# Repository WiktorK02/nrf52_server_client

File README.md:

to do:
remove delay from functions

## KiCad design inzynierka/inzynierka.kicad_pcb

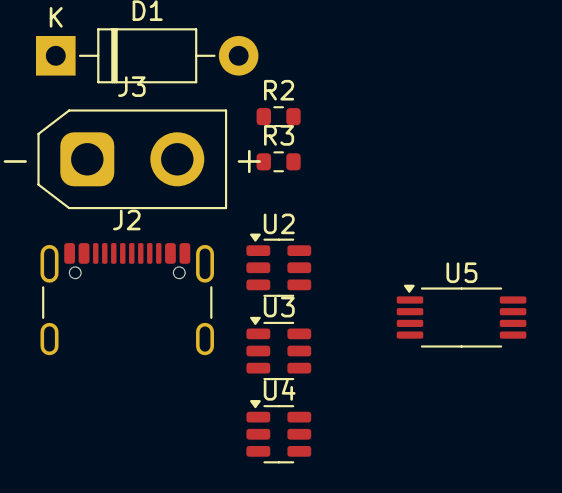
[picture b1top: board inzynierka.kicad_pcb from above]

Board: 2 copper layers, 9 parts (0 on the bottom side), 9 nets, no tracks yet.

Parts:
D1: SB220; D_DO-41_SOD81_P10.16mm_Horizontal
J2: USB_C_Receptacle_USB2.0_16P; USB_C_Receptacle_GCT_USB4105-xx-A_16P_TopMnt_Horizontal
J3: con; AMASS_XT30UPB-F_1x02_P5.0mm_Vertical
R2, R3: 5.1k; R_0603_1608Metric
U2: USBLC6-2SC6; SOT-23-6
U3: TP4057; TSOT-23-6
U4: DW01A; SOT-23-6
U5: dual nmos; TSSOP-8_4.4x3mm_P0.65mm

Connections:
5V: D1.2 (A), J2.A4 (VBUS), J2.A9 (VBUS), J2.B4 (VBUS), J2.B9 (VBUS), U2.5 (VBUS), U3.4 (V_{CC})
+BAT: J3.1, U3.3 (BAT)
-BAT: J2.A1 (GND), J2.A12 (GND), J2.B1 (GND), J2.B12 (GND), J2.S1 (SHIELD), J3.2, R2.2, R3.2, U2.2 (GND), U3.2 (GND), U4.6 (GND), U5.2 (S1), U5.3 (S1), U5.6 (S2), U5.7 (S2)
unnamed: J2.A5 (CC1), R3.1
unnamed: J2.B5 (CC2), R2.1
unnamed: J2.A6 (D+), J2.B6 (D+), U2.3 (I/O2)
unnamed: J2.A7 (D-), J2.B7 (D-), U2.1 (I/O1)
unnamed: U4.3 (OC), U5.4 (G1)
unnamed: U4.1 (OD), U5.5 (G2)

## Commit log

2025-10-25 Add switch input handling and LED toggle functionality
    Added support for a switch input on PIN_022 and modified the server-client communication to toggle an LED based on switch events. Implemented debounce logic for the switch and updated logging for swi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
2025-10-25 Add to-do item to remove delay from functions
2025-10-26 Refactor LED handling, improve code clarity, remove delay
    Refactor LED blinking and delay handling for better performance and responsiveness. Update comments for clarity and maintainability.
2025-10-29 Enhance OLED display functionality and client listing, add keyboard hid
    Refactor OLED display functions and add client list display.
2025-10-30 Change debounce and add key press/hold functinality
    Updated comments and code for clarity and consistency. Refactored OLED display functions and button handling for better readability and structure.
2025-11-04 Refactor keyboard button handling and OLED display
    Refactor button handling and OLED display logic for keyboard input. Update comments and improve code readability.
2025-11-12 Remove bugs with server being umounted and battery reading
2025-11-14 Add eeprom functionalities
2025-11-16 Implement factory reset for server and client
    Added factory reset functionality for both server and client, including EEPROM wipe methods and a reset button.
2025-11-16 Improve battery charging animation handling
    Refactor battery charging animation and display logic
